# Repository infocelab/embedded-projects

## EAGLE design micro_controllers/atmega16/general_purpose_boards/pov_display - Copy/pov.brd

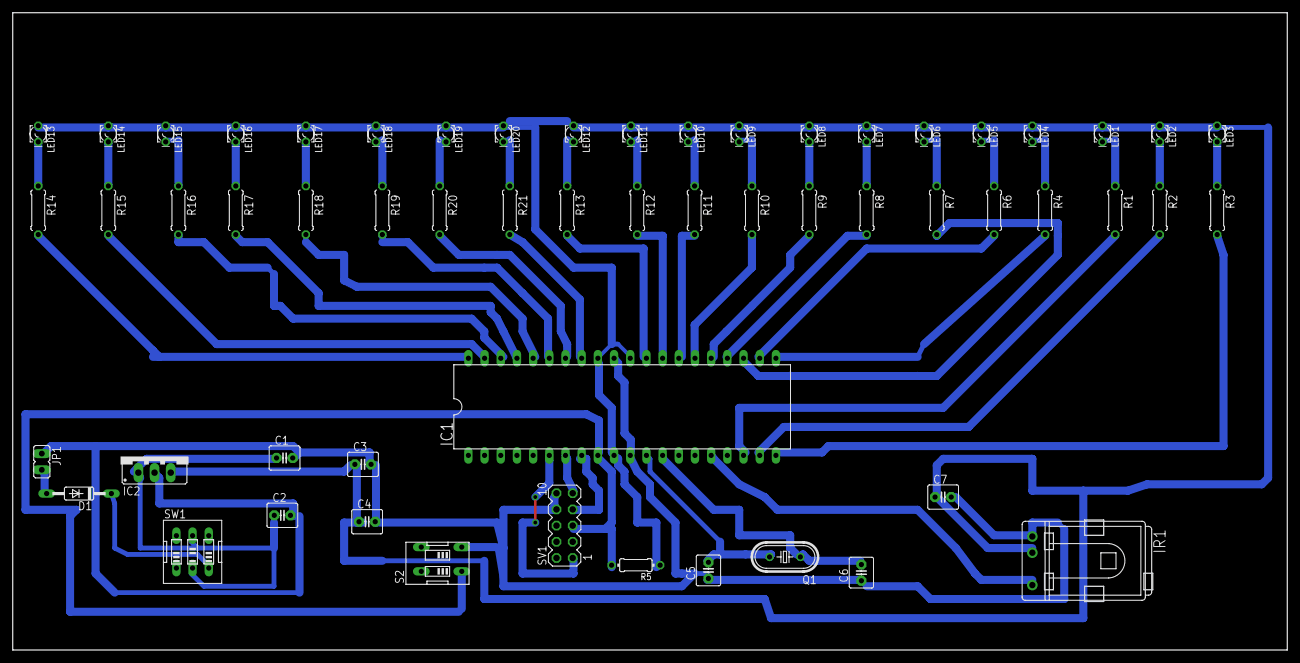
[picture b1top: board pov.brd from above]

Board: 2 copper layers, 200.0 x 100.0 mm, 57 parts (0 on the bottom side), 52 nets.

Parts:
C1, C7: 470uF; C2.5-4
C2, C4: 0.1uF; C2.5-4
C3: 4.7uF; C2.5-4
C5, C6: 33pF; C2.5-4
D1: 1N4148DO35-10; DO35-10
IC1: MEGA163LP; DIL40
IC2: 78XXS
IR1: TSOP1733TB1; TSOP17_TB1
JP1: JP1
LED1, LED2, LED3, LED4, LED5, LED6, LED7, LED8, LED9, LED10, LED11, LED12, LED13, LED14, LED15, LED16, LED17, LED18, LED19, LED20: LED_LD260
Q1: 16MHZ; HC49U-V
R1, R2, R3, R4, R6, R7, R8, R9, R10, R11, R12, R13, R14, R15, R16, R17, R18, R19, R20, R21: 0207/7
R5: 10K; 0204/7
S2: EDG-02
SV1: MA05-2
SW1: EDG-03

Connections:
+5V: C3.1, C4.1, C7.1, IC1.10, IC1.30, IC1.32, IC2.OUT, IR1.VS, LED1.A, LED2.A, LED3.A, LED4.A, LED5.A, LED6.A, LED7.A, LED8.A, LED9.A, LED10.A, LED11.A, LED12.A, LED13.A, LED14.A, LED15.A, LED16.A, LED17.A, LED18.A, LED19.A, LED20.A, R5.1
GND: C1.2, C2.2, C3.2, C4.2, C5.1, C6.1, C7.2, IC1.11, IC1.31, IC2.GND, IR1.GND, JP1.1, S2.2, SV1.8, SV1.10
unnamed: D1.A, JP1.2
unnamed: LED12.K, R13.1
unnamed: C5.2, IC1.12, Q1.2
unnamed: C6.2, IC1.13, Q1.1
unnamed: LED1.K, R1.1
unnamed: IC1.9, R5.2, S2.1, SV1.5
unnamed: IC1.22, R6.2
unnamed: D1.C, SW1.3
unnamed: C1.1, C2.1, IC2.IN, SW1.2, SW1.5
unnamed: IC1.28, R12.2
unnamed: LED10.K, R11.1
unnamed: IC1.26, R10.2
unnamed: LED9.K, R10.1
unnamed: IC1.25, R9.2
unnamed: LED8.K, R9.1
unnamed: LED7.K, R8.1
unnamed: IC1.6, SV1.1
unnamed: IC1.7, SV1.9
unnamed: IC1.8, SV1.7
unnamed: IC1.23, R7.2
unnamed: IC1.33, R21.2
unnamed: IC1.34, R20.2
unnamed: IC1.35, R19.2
unnamed: IC1.36, R18.2
unnamed: IC1.37, R17.2
unnamed: IC1.38, R16.2
unnamed: IC1.39, R15.2
unnamed: IC1.40, R14.2
unnamed: IC1.24, R8.2
unnamed: IC1.27, R11.2
unnamed: IC1.29, R13.2
unnamed: LED6.K, R7.1
unnamed: LED20.K, R21.1
unnamed: LED19.K, R20.1
unnamed: LED18.K, R19.1
unnamed: LED17.K, R18.1
unnamed: LED15.K, R16.1
unnamed: LED13.K, R14.1
unnamed: LED16.K, R17.1
unnamed: LED14.K, R15.1
unnamed: LED5.K, R6.1
unnamed: LED11.K, R12.1
unnamed: LED2.K, R2.1
unnamed: LED3.K, R3.1
unnamed: LED4.K, R4.1
unnamed: IC1.20, R3.2
unnamed: IC1.21, R4.2
unnamed: IC1.19, R2.2
unnamed: IC1.18, R1.2
unnamed: IC1.16, IR1.VO

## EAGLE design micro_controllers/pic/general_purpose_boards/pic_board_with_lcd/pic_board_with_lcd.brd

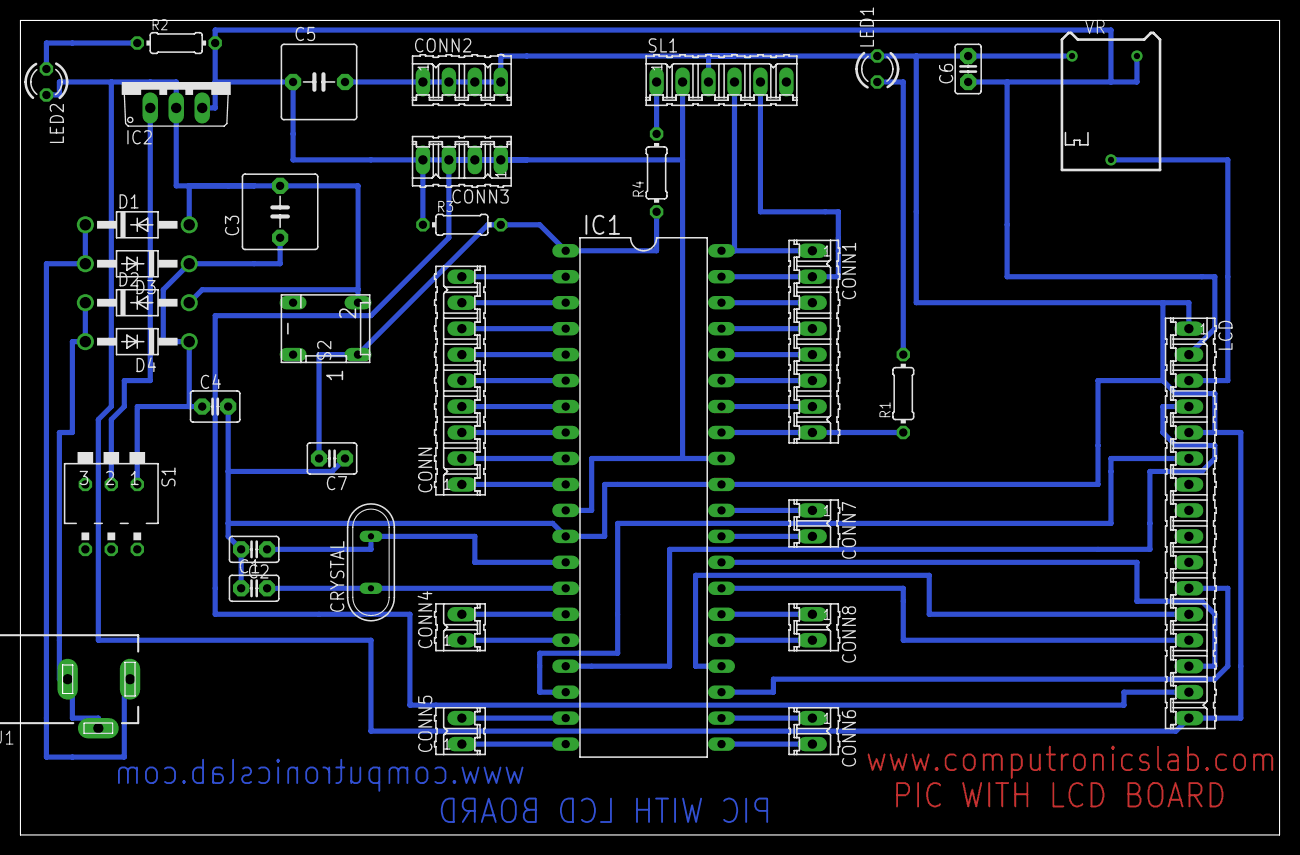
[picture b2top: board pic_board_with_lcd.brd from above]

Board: 2 copper layers, 123.2 x 79.7 mm, 35 parts (0 on the bottom side), 46 nets.

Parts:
C1, C2, C6: 22pf; C2.5-2
C3: 100uf; C5B7.2
C4, C7: 0.1uf; C2.5-3
C5: 4.7uf; C5B7.2
CONN: 9 pin; 09P
CONN1: 7 pin; 08P
CONN2, CONN3: 4 pin; 04P
CONN4: 02P
CONN5, CONN6, CONN7, CONN8: 2pin; 02P
CRYSTAL: 8MHZ; QS
D1, D2, D3, D4: 1N4007; DO41-10
IC1: PIC16f877a; DIL40
IC2: 7805TV; TO220V
J1: DCJ0303
LCD: 16P
LED1, LED2: 3mm; LED3MM
R1, R2: 220E; 0204/7
R3: 10K; 0204/7
R4: 68E; 0204/7
S1: DA-03
S2: push switch; DP-02
SL1: 06P
VR: 10k; RTRIM64P

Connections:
unnamed: C2.1, CRYSTAL.2, IC1.13
unnamed: C1.2, CRYSTAL.1, IC1.14
unnamed: LED1.A, R1.2
unnamed: CONN.1, IC1.10
unnamed: CONN.2, IC1.9
unnamed: CONN.3, IC1.8
unnamed: CONN.4, IC1.7
unnamed: CONN.5, IC1.6
unnamed: CONN.6, IC1.5
unnamed: CONN.7, IC1.4
unnamed: CONN.8, IC1.3
unnamed: CONN.9, IC1.2
unnamed: CONN5.1, IC1.20
unnamed: CONN5.2, IC1.19
unnamed: CONN4.1, IC1.16
unnamed: CONN4.2, IC1.15
unnamed: IC1.17, LCD.4
unnamed: CONN6.1, IC1.22
unnamed: CONN1.1, IC1.40, SL1.4
unnamed: CONN1.2, IC1.39, SL1.5
unnamed: CONN1.3, IC1.38
unnamed: CONN1.4, IC1.37
unnamed: CONN1.5, IC1.36
unnamed: CONN1.6, IC1.35
unnamed: CONN1.7, IC1.34
unnamed: CONN6.2, IC1.21
unnamed: CONN7.1, IC1.30
unnamed: CONN7.2, IC1.29
unnamed: CONN1.8, IC1.33, R1.1
unnamed: C3.1, C4.1, D3.C, D4.C, S1.1
unnamed: D2.C, D4.A, J1.2, J1.3
unnamed: D1.C, D3.A, J1.1
unnamed: C5.1, C6.1, CONN3.1, CONN3.2, CONN3.3, CONN3.4, IC1.11, IC1.32, IC2.3, LCD.2, LCD.15, R2.2, R3.1, SL1.2, VR.3
unnamed: LED2.A, R2.1
unnamed: C1.1, C2.2, C3.2, C4.2, C5.2, C6.2, C7.1, CONN2.1, CONN2.2, CONN2.3, CONN2.4, D1.A, D2.A, IC1.12, IC1.31, IC2.2, LCD.1, LCD.5, LCD.16, LED1.K, LED2.K, S2.2, SL1.3, VR.1
unnamed: CONN8.2, IC1.25
unnamed: IC1.23, LCD.11
unnamed: C7.2, IC1.1, R3.2, R4.1, S2.1
unnamed: LCD.3, VR.2
unnamed: IC1.24, LCD.12
unnamed: IC1.27, LCD.13
unnamed: IC1.28, LCD.14
unnamed: IC2.1, S1.2
unnamed: R4.2, SL1.1
unnamed: IC1.18, LCD.6
unnamed: CONN8.1, IC1.26

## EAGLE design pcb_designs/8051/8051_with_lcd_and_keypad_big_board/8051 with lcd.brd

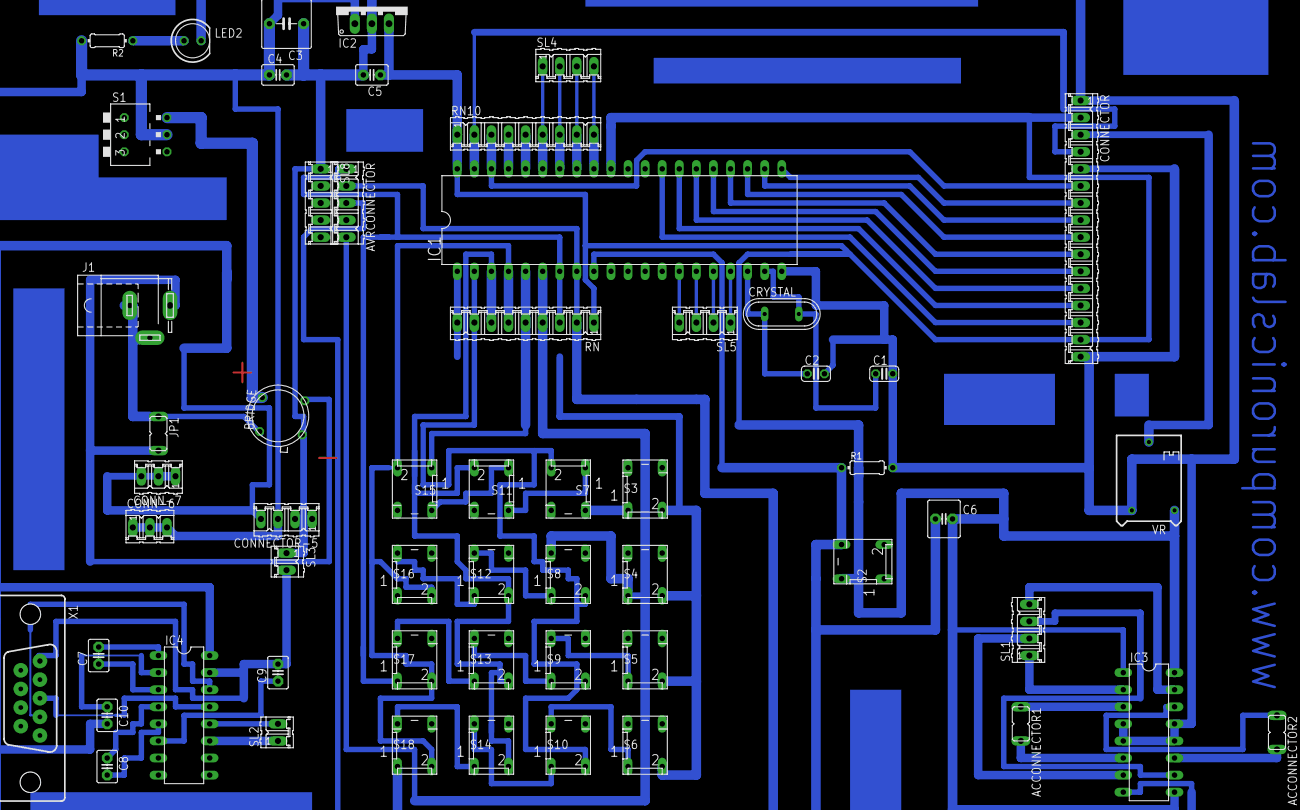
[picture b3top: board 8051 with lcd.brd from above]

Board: 2 copper layers, 56 parts (0 on the bottom side), 69 nets.

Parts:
ACCONNECTOR1, ACCONNECTOR2: motor; JP1
AVRCONNECTOR: 05P
BRIDGE: TO39/4
C1, C2: 33pf; C025-024X044
C3: 470uf; C5B7.2
C4: .01uf; C2.5-3
C5: 4.7uf; C2.5-3
C6: 0.1uf; C2.5-6
C7, C8, C9, C10: 0.1uf; C2.5-3
CONN-6, CONN-7: 3 pin; 03P
CONNECTOR: LCD; 16P
CONNECTOR-5: 4 pin; 04P
CRYSTAL: 11.0592 mhz; QS
IC1: AT89S51; DIL40
IC2: 7805TV; TO220V
IC3: L293D; DIL16
IC4: MAX232; DIL16
J1: SPC4077
JP1: TRANSFORMER; JP1
LED2: 5mm; LED5MM
R1: 10k; 0204/7
R2: 560E; 0204/7
RN: 10K; 09P
RN10: 10 k; 09P
S1: ON/ OFF SWITCH; DA-03
S2, S3, S4: push switch; DP-02
S5, S6, S7, S8, S9, S10, S11, S12, S13, S14, S15, S16, S17, S18: DP-02
SL1: 4 pin; 04P
SL2: 2 pin; 02P
SL3: jumper; 02P
SL4, SL5: 04P
SL8: 05P
VR: 10k; RTRIM64P
X1: DB 9 FEMALE; H2M09ST

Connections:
unnamed: C2.1, CRYSTAL.1, IC1.18
unnamed: C1.1, CRYSTAL.2, IC1.19
unnamed: C9.2, IC4.15, SL3.2, X1.1
unnamed: C7.2, IC4.1
unnamed: BRIDGE.2, J1.3, JP1.2
unnamed: IC1.17, SL5.1
unnamed: IC1.16, SL5.2
unnamed: IC1.15, SL5.3
unnamed: IC1.14, SL5.4
unnamed: AVRCONNECTOR.3, C6.1, IC1.9, R1.1, S2.3
unnamed: AVRCONNECTOR.5, IC1.6, RN.4, S4.1, S8.4
unnamed: BRIDGE.4, J1.1, J1.2, JP1.1
unnamed: IC1.5, RN.5, S15.1
unnamed: IC1.4, RN.6, S15.2, S16.2, S17.2, S18.2
unnamed: IC1.3, RN.7, S11.2, S12.2, S13.2, S14.2
unnamed: IC1.2, RN.8, S7.2, S8.2, S9.2, S10.2
unnamed: IC1.1, RN.9, S3.2, S4.2, S5.2, S6.2
unnamed: C7.1, IC4.3
unnamed: IC1.37, RN10.4
unnamed: IC1.36, RN10.5
unnamed: IC1.35, RN10.6, SL4.1
unnamed: IC1.34, RN10.7, SL4.2
unnamed: IC1.33, RN10.8, SL4.3
unnamed: IC1.32, RN10.9, SL4.4
unnamed: CONNECTOR.7, IC1.21
unnamed: CONNECTOR.8, IC1.22
unnamed: CONNECTOR.9, IC1.23
unnamed: S3.1, S7.4
unnamed: S7.1, S11.4
unnamed: CONNECTOR.12, IC1.26
unnamed: S11.1, S15.4
unnamed: S8.1, S12.4
unnamed: CONNECTOR.3, VR.2
unnamed: S12.1, S16.4
unnamed: IC3.2, SL1.1
unnamed: AVRCONNECTOR.1, IC1.7, RN.3, S17.1
unnamed: C3.2, C4.1, CONN-6.1, CONN-6.2, CONN-6.3, CONNECTOR-5.3, IC2.1, IC3.8, R2.2, S1.5
unnamed: S13.1, S17.4
unnamed: AVRCONNECTOR.2, IC1.8, RN.2, S18.1
unnamed: BRIDGE.3, S1.6
unnamed: CONNECTOR.6, IC1.38, RN10.3
unnamed: S14.1, S18.4
unnamed: S10.1, S14.4
unnamed: CONNECTOR.10, IC1.24
unnamed: CONNECTOR.11, IC1.25
unnamed: C8.1, IC4.4
unnamed: CONNECTOR.13, IC1.27
unnamed: CONNECTOR.14, IC1.28
unnamed: ACCONNECTOR1.1, IC3.3
unnamed: CONNECTOR.4, IC1.39, RN10.2
unnamed: ACCONNECTOR1.2, IC3.6
unnamed: ACCONNECTOR2.1, IC3.14
unnamed: ACCONNECTOR2.2, IC3.11
unnamed: S5.1, S9.4
unnamed: S6.1, S10.4
unnamed: S9.1, S13.4
unnamed: IC3.7, SL1.2
unnamed: IC3.10, SL1.3
unnamed: IC3.15, SL1.4
unnamed: C8.2, IC4.5
unnamed: C9.1, IC4.6
unnamed: LED2.A, R2.1
unnamed: BRIDGE.1, C1.2, C2.2, C3.1, C4.2, C5.2, CONNECTOR.1, CONNECTOR.5, CONNECTOR.16, CONNECTOR-5.1, CONNECTOR-5.2, IC1.20, IC2.2, IC3.4, IC3.5, IC3.12, IC3.13, LED2.K, R1.2, SL3.1, SL8.1, VR.3
unnamed: C10.1, IC4.2
unnamed: C5.1, C6.2, C10.2, CONN-7.1, CONN-7.2, CONN-7.3, CONNECTOR.2, CONNECTOR.15, CONNECTOR-5.4, IC1.31, IC1.40, IC2.3, IC3.1, IC3.9, IC3.16, IC4.16, RN.1, RN10.1, S2.4, VR.1
unnamed: IC4.13, X1.3
unnamed: IC4.14, X1.4
unnamed: IC4.11, SL2.1
unnamed: IC4.12, SL2.2

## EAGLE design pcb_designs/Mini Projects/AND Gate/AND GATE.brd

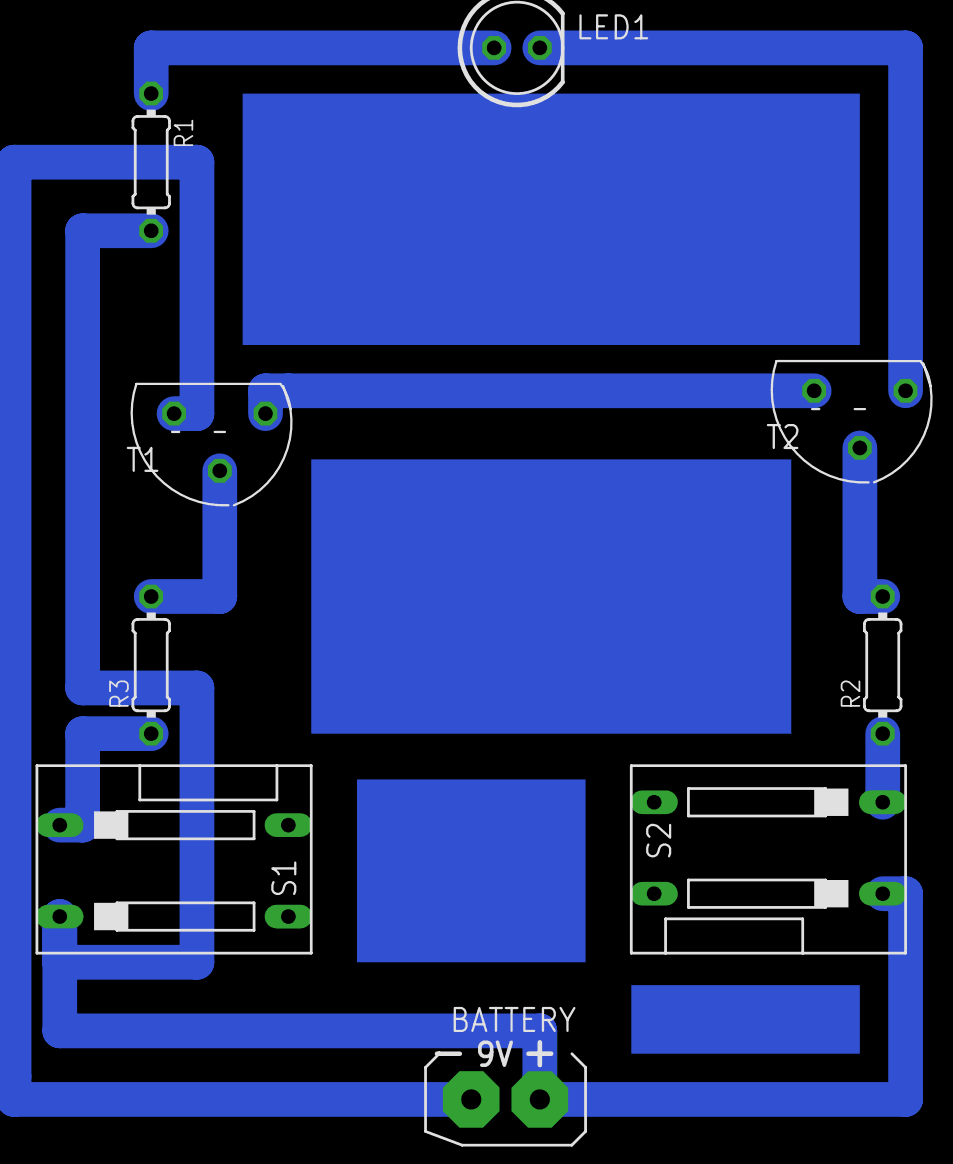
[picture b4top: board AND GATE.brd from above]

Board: 2 copper layers, 9 parts (0 on the bottom side), 9 nets.

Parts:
BATTERY: 9V; AB9V
LED1: 5MM; LED5MM
R1: 220E; 0204/7
R2, R3: 10K; 0204/7
S1, S2: PUSH SWITCH; DS-02
T1, T2: BC547; TO92

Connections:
unnamed: T1.3, T2.1
unnamed: R2.2, T2.2
unnamed: R3.2, T1.2
unnamed: LED1.K, T2.3
unnamed: LED1.A, R1.1
unnamed: R2.1, S2.2
unnamed: R3.1, S1.1
unnamed: BATTERY.+, R1.2, S1.2, S2.1
unnamed: BATTERY.-, T1.1

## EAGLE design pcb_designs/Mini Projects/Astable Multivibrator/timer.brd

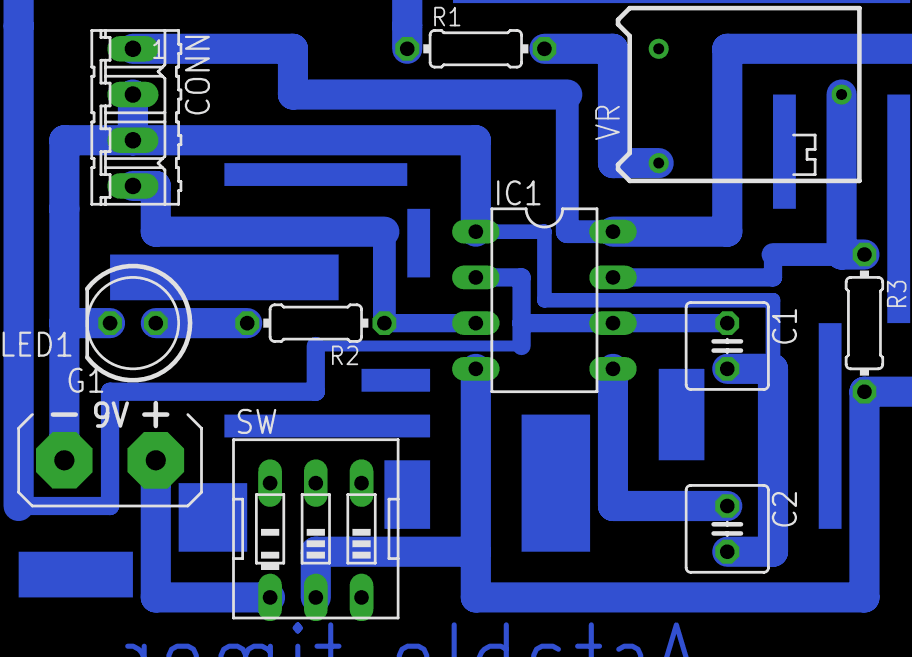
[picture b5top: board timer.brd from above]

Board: 2 copper layers, 11 parts (0 on the bottom side), 9 nets.

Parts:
C1: 100uf; C025-050X050
C2: 0.1uf; C025-050X050
CONN: 4 PIN; 04P
G1: AB9V
IC1: NE555; DIL-08
LED1: 5mm; LED5MM
R1: 1K; 0204/7
R2: 220E; 0204/7
R3: 4.7K; 0204/7
SW: on/of button; EDG-03
VR: 100k; RTRIM64P

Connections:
unnamed: C1.1, IC1.2, IC1.6, R1.1
unnamed: C2.1, IC1.5
unnamed: IC1.7, R3.1, VR.2
unnamed: CONN.4, IC1.3, R2.1
unnamed: LED1.A, R2.2
unnamed: G1.+, SW.1
unnamed: R1.2, VR.1
unnamed: C1.2, C2.2, CONN.2, CONN.3, G1.-, IC1.1, LED1.K
unnamed: CONN.1, IC1.4, IC1.8, R3.2, SW.2

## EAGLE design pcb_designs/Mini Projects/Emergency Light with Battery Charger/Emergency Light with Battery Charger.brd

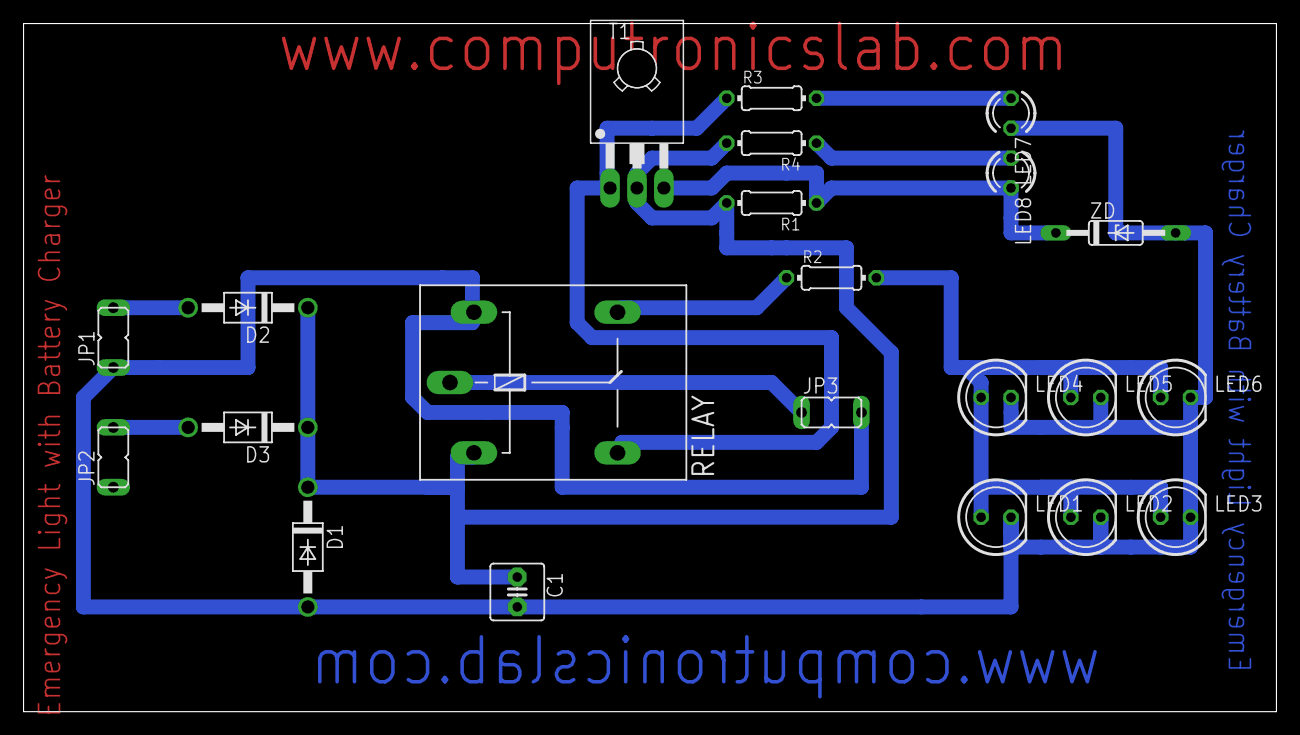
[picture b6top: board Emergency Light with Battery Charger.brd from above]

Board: 2 copper layers, 106.3 x 58.4 mm, 22 parts (0 on the bottom side), 11 nets.

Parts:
C1: 100uf; C2.5-5
D1, D2, D3: 1N4007; DO41-10
JP1, JP2: ac connector; JP1
JP3: battery; JP1
LED1, LED2, LED3, LED4, LED5, LED6: 5mm; LED5MM
LED7, LED8: 3mm; LED3MM
R1: 100E; 0204/7
R2: 47E; 0204/7
R3, R4: 330E; 0204/7
RELAY: 6V; G5LE
T1: BD139; TO126
ZD: 6.8 V; DO35Z10

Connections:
unnamed: D2.A, JP1.2
unnamed: D3.A, JP2.2
unnamed: LED7.A, R3.2
unnamed: C1.2, D1.A, JP1.1, JP3.2, LED1.K, LED2.K, LED3.K, LED4.K, LED5.K, LED6.K, LED7.K, RELAY.2, ZD.A
unnamed: LED8.K, R1.1, T1.3, ZD.C
unnamed: R3.1, RELAY.S, T1.1
unnamed: JP3.1, RELAY.P
unnamed: R2.1, RELAY.O
unnamed: LED1.A, LED2.A, LED3.A, LED4.A, LED5.A, LED6.A, R2.2
unnamed: C1.1, D1.C, D2.C, D3.C, R1.2, R4.2, RELAY.1, T1.2
unnamed: LED8.A, R4.1
